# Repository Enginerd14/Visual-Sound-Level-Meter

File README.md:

# Visual-Sound-Level-Meter

A visual sound level meter is a device that uses LEDs to react to and display sound levels. 

I decided I want to make this because firstly I think they look really cool and secondly, they have a real world purpose. People listen to music too loud. There are studies linking hearing loss to earbuds use and going to concerts and being loud environment as a whole. I wanted to make this device to alet people when the environemnt is too loud and potentially damaging to their hearing. 

## PCB

## CAD

## Schematic

## BOM

| Component              | Quantity         | Cost (£) | Link |
|------------------------|------------------|----------|------|
| LM3915                | 6                | 2.99     | [LM3915 10Pcs](https://www.aliexpress.com/item/32946954434.html) |
| TDA7266               | 1                | 2.29     | [TDA7266](https://www.aliexpress.com/item/1005010770316681.html) |
| Mic                   | 1                | 1.29     | [electret mic](https://www.aliexpress.com/item/4000037505554.html) |
| Passive components    | Already have     | ~        | ~ |
| **Total cost**        |                  | **£6.57**| $8.72     |

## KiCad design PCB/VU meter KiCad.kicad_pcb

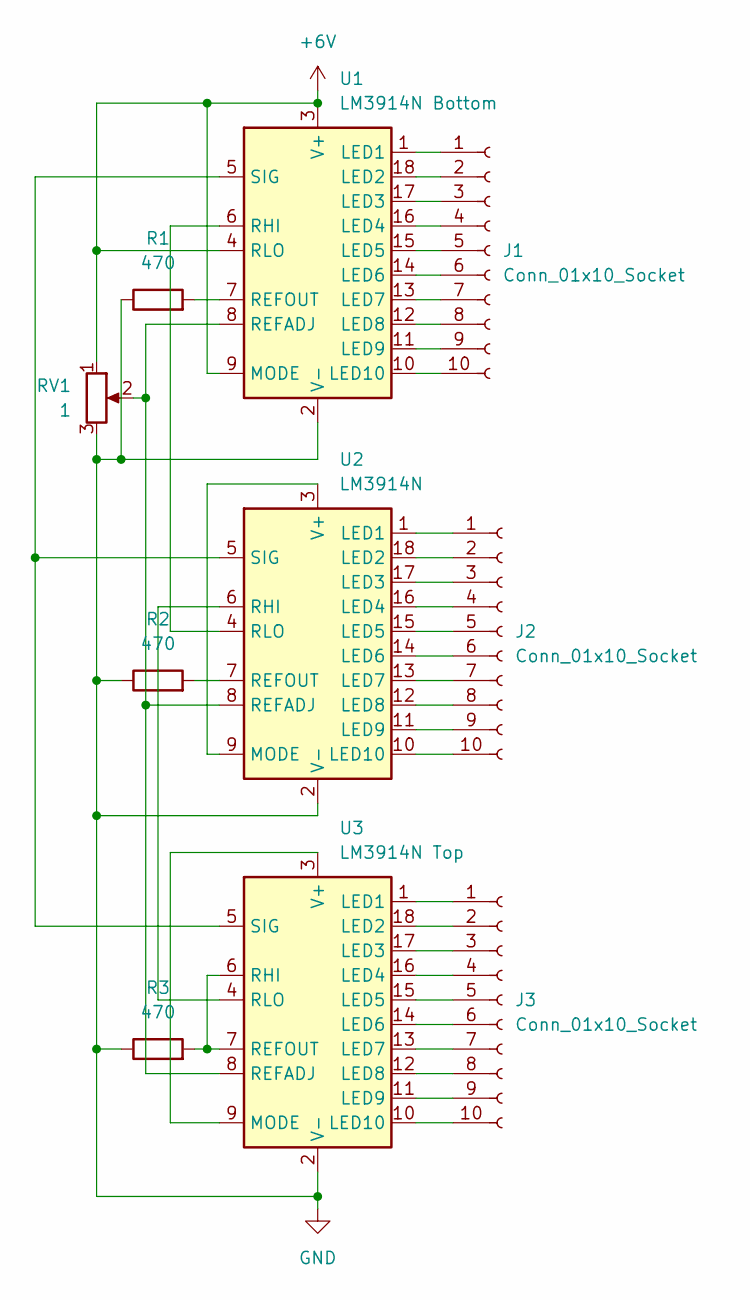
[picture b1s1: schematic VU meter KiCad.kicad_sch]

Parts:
J1, J2, J3: Conn_01x10_Socket; PinHeader_1x10_P2.54mm_Vertical
R1, R2, R3: 470; R_Axial_DIN0204_L3.6mm_D1.6mm_P5.08mm_Horizontal
RV1: 1; Potentiometer_Bourns_3296W_Vertical
U1: LM3914N Bottom; DIP-18_W7.62mm
U2: LM3914N; DIP-18_W7.62mm
U3: LM3914N Top; DIP-18_W7.62mm

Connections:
+6V: RV1.1, U1.3 (V+), U1.4 (RLO), U1.9 (MODE)
GND: R1.1, R2.1, R3.1, RV1.3, U1.2 (V-), U2.2 (V-), U3.2 (V-)
unnamed: J1.1, U1.1 (LED1)
unnamed: J1.2, U1.18 (LED2)
unnamed: J1.3, U1.17 (LED3)
unnamed: J1.4, U1.16 (LED4)
unnamed: J1.5, U1.15 (LED5)
unnamed: J1.6, U1.14 (LED6)
unnamed: J1.7, U1.13 (LED7)
unnamed: J1.8, U1.12 (LED8)
unnamed: J1.9, U1.11 (LED9)
unnamed: J1.10, U1.10 (LED10)
unnamed: J2.1, U2.1 (LED1)
unnamed: J2.2, U2.18 (LED2)
unnamed: J2.3, U2.17 (LED3)
unnamed: J2.4, U2.16 (LED4)
unnamed: J2.5, U2.15 (LED5)
unnamed: J2.6, U2.14 (LED6)
unnamed: J2.7, U2.13 (LED7)
unnamed: J2.8, U2.12 (LED8)
unnamed: J2.9, U2.11 (LED9)
unnamed: J2.10, U2.10 (LED10)
unnamed: J3.1, U3.1 (LED1)
unnamed: J3.2, U3.18 (LED2)
unnamed: J3.3, U3.17 (LED3)
unnamed: J3.4, U3.16 (LED4)
unnamed: J3.5, U3.15 (LED5)
unnamed: J3.6, U3.14 (LED6)
unnamed: J3.7, U3.13 (LED7)
unnamed: J3.8, U3.12 (LED8)
unnamed: J3.9, U3.11 (LED9)
unnamed: J3.10, U3.10 (LED10)
unnamed: RV1.2, U1.8 (REFADJ), U2.8 (REFADJ), U3.8 (REFADJ)
unnamed: R1.2, U1.7 (REFOUT)
unnamed: U1.6 (RHI), U2.4 (RLO)
unnamed: U1.5 (SIG), U2.5 (SIG), U3.5 (SIG)
unnamed: U2.3 (V+), U2.9 (MODE)
unnamed: R2.2, U2.7 (REFOUT)
unnamed: U2.6 (RHI), U3.4 (RLO)
unnamed: U3.3 (V+), U3.9 (MODE)
unnamed: R3.2, U3.6 (RHI), U3.7 (REFOUT)

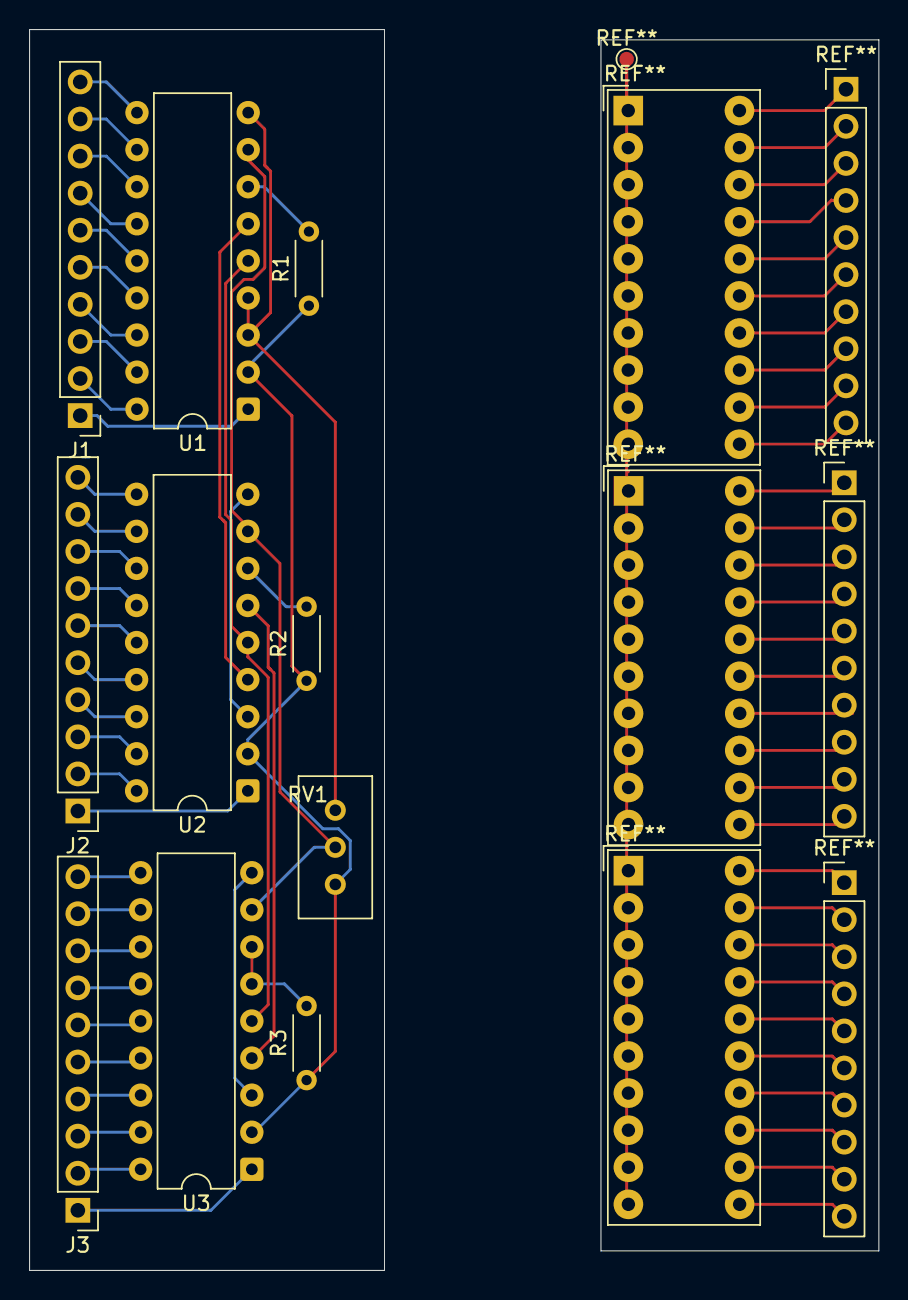
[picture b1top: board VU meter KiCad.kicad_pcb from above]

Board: 2 copper layers, 58.2 x 85.0 mm, 10 parts (0 on the bottom side), 41 nets.

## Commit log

2025-12-25 Add research and prototyping details for VU meter
    Documented research on VU meter methods, including PIC, LED bar graph with LM39_ _ IC, and transistors. Added historical context for LEDs and microphones, along with iterations of LM3915 circuit prot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
2025-12-25 Update JOURNAL.md with VU meter research and iterations
    Documented research on VU meter methods, including PIC, LED bar graph with LM39_ _, and transistor usage. Added iterations of LM3915 and LM386 circuits with troubleshooting notes.
2025-12-25 Document circuit iterations and PCB design process
    Added detailed descriptions of circuit iterations and PCB design.
2025-12-25 Update JOURNAL.md with LM3915 circuit attempts
    Documented multiple attempts at creating a cascading circuit with the LM3915, detailing successes and failures.
2025-12-25 Add PCB production process to JOURNAL.md
    Documented the process of producing a PCB, including steps for printing the circuit, cutting the board, and developing the tracks.
2025-12-26 Revise journal entries with dates and details
    Updated journal entries with specific dates, hours spent, and detailed descriptions of the research and development process for the VU meter project.
2025-12-26 Revise JOURNAL.md with new research and hours
    Updated journal entries with hours spent and details on research methods for VU meter project.
2025-12-27 Revise hours and descriptions in JOURNAL.md
    Updated hours spent on various tasks and refined descriptions throughout the journal entries.
2025-12-27 Document project specifications and update hours
    Added a project specification section outlining desired features and updated hours spent.
2025-12-27 Updated JOURNAL.md
2025-12-27 Expand README with project details and components
    Added detailed project description, PCB, CAD, schematic, and BOM sections.
2025-12-28 Create Cad
2025-12-28 Create pcb
2026-02-08 Update journal and content for project progress
2026-02-08 Update README with new images and BOM section
    Added additional images for PCB, CAD, and Schematic sections.
2026-03-28 Update BOM with new components and costs
2026-05-25 Enhance README with purpose and images
    Added an image and expanded on the purpose of the sound level meter.
